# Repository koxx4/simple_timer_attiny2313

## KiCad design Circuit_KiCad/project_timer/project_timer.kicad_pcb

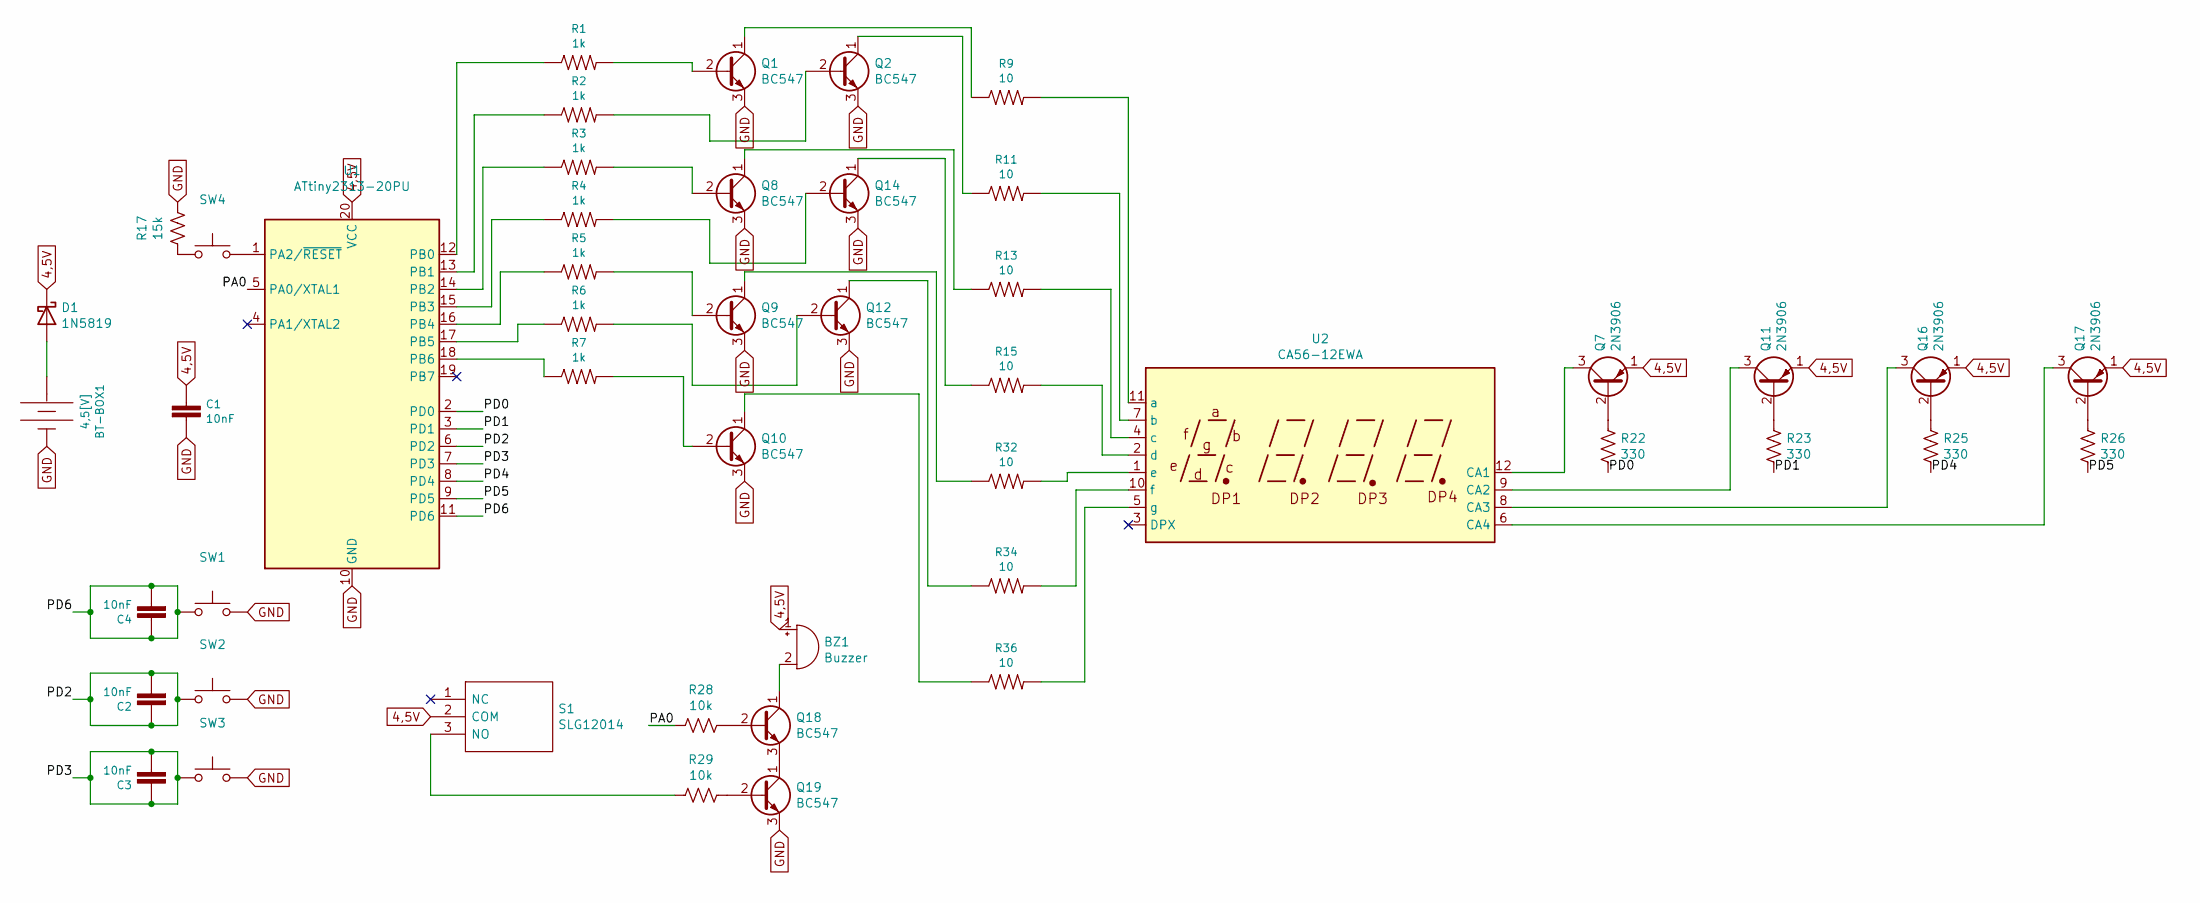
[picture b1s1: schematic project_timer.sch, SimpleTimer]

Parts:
BT-BOX1: 4,5[V]; BatteryHolder_Keystone_2479_3xAAA
BZ1: Buzzer; Buzzer_12x9.5RM7.6
C1, C2, C3, C4: 10nF; C_Disc_D5.0mm_W2.5mm_P2.50mm_1mm-hole
D1: 1N5819; D_DO-15_P10.16mm_Horizontal
Q1, Q2, Q8, Q9, Q10, Q12, Q14, Q18, Q19: BC547; TO-92_HandSolder_1mm
Q7, Q11, Q16, Q17: 2N3906; TO-92_HandSolder_1mm
R1, R2, R3, R4, R5, R6, R7: 1k; R_Axial_DIN0207_L6.3mm_D2.5mm_P2.54mm_Vertical_1mm-hole
R9, R11, R13, R15, R32, R34, R36: 10; R_Axial_DIN0207_L6.3mm_D2.5mm_P2.54mm_Vertical_1mm-hole
R17: 15k; R_Axial_DIN0207_L6.3mm_D2.5mm_P2.54mm_Vertical_1mm-hole
R22, R23, R25, R26: 330; R_Axial_DIN0207_L6.3mm_D2.5mm_P2.54mm_Vertical_1mm-hole
R28, R29: 10k; R_Axial_DIN0207_L6.3mm_D2.5mm_P2.54mm_Vertical_1mm-hole
S1: SLG12014; SLG12014_Bigger; Manufacturer_Part_Number SLG12014; Mouser Part Number 642-SLG12014
SW1, SW2, SW3, SW4: SW_MEC_5G; SW_PUSH_6mm
U1: ATtiny2313-20PU; DIP-20_W7.62mm_Socket_1mm-hole
U2: CA56-12EWA

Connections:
4,5V: BZ1.1 (-), C1.1, D1.1 (K), Q7.1 (E), Q11.1 (E), Q16.1 (E), Q17.1 (E), S1.2 (COM), U1.20 (VCC)
/PA0: R28.2, U1.5 (PA0/XTAL1)
/PD0: R22.2, U1.2 (PD0)
/PD1: R23.2, U1.3 (PD1)
/PD2: C2.1, C2.2, SW2.1 (A), SW2.2 (A), U1.6 (PD2)
/PD3: C3.1, C3.2, SW3.1 (A), SW3.2 (A), U1.7 (PD3)
/PD4: R25.2, U1.8 (PD4)
/PD5: R26.2, U1.9 (PD5)
/PD6: C4.1, C4.2, SW1.1 (A), SW1.2 (A), U1.11 (PD6)
GND: BT-BOX1.2 (-), C1.2, Q1.3 (E), Q2.3 (E), Q8.3 (E), Q9.3 (E), Q10.3 (E), Q12.3 (E), Q14.3 (E), Q19.3 (E), R17.2, SW1.3 (B), SW1.4 (B), SW2.3 (B), SW2.4 (B), SW3.3 (B), SW3.4 (B), U1.10 (GND)
unnamed: BT-BOX1.1 (+), D1.2 (A)
unnamed: BZ1.2 (+), Q18.1 (C)
unnamed: Q1.1 (C), R9.1
unnamed: Q1.2 (B), R1.2
unnamed: Q2.1 (C), R11.1
unnamed: Q2.2 (B), R2.2
unnamed: Q7.2 (B), R22.1
unnamed: Q7.3 (C), U2.12 (CA1)
unnamed: Q8.1 (C), R13.1
unnamed: Q8.2 (B), R3.2
unnamed: Q9.1 (C), R32.1
unnamed: Q9.2 (B), R5.2
unnamed: Q10.1 (C), R36.1
unnamed: Q10.2 (B), R7.2
unnamed: Q11.2 (B), R23.1
unnamed: Q11.3 (C), U2.9 (CA2)
unnamed: Q12.1 (C), R34.1
unnamed: Q12.2 (B), R6.2
unnamed: Q14.1 (C), R15.1
unnamed: Q14.2 (B), R4.2
unnamed: Q16.2 (B), R25.1
unnamed: Q16.3 (C), U2.8 (CA3)
unnamed: Q17.2 (B), R26.1
unnamed: Q17.3 (C), U2.6 (CA4)
unnamed: Q18.2 (B), R28.1
unnamed: Q18.3 (E), Q19.1 (C)
unnamed: Q19.2 (B), R29.1
unnamed: R1.1, U1.12 (PB0)
unnamed: R2.1, U1.13 (PB1)
unnamed: R3.1, U1.14 (PB2)
unnamed: R4.1, U1.15 (PB3)
unnamed: R5.1, U1.16 (PB4)
unnamed: R6.1, U1.17 (PB5)
unnamed: R7.1, U1.18 (PB6)
unnamed: R9.2, U2.11 (a)
unnamed: R11.2, U2.7 (b)
unnamed: R13.2, U2.4 (c)
unnamed: R15.2, U2.2 (d)
unnamed: R17.1, SW4.1 (A), SW4.2 (A)
unnamed: R29.2, S1.3 (NO)
unnamed: R32.2, U2.1 (e)
unnamed: R34.2, U2.10 (f)
unnamed: R36.2, U2.5 (g)
unnamed: SW4.3 (B), SW4.4 (B), U1.1 (PA2/~RESET)

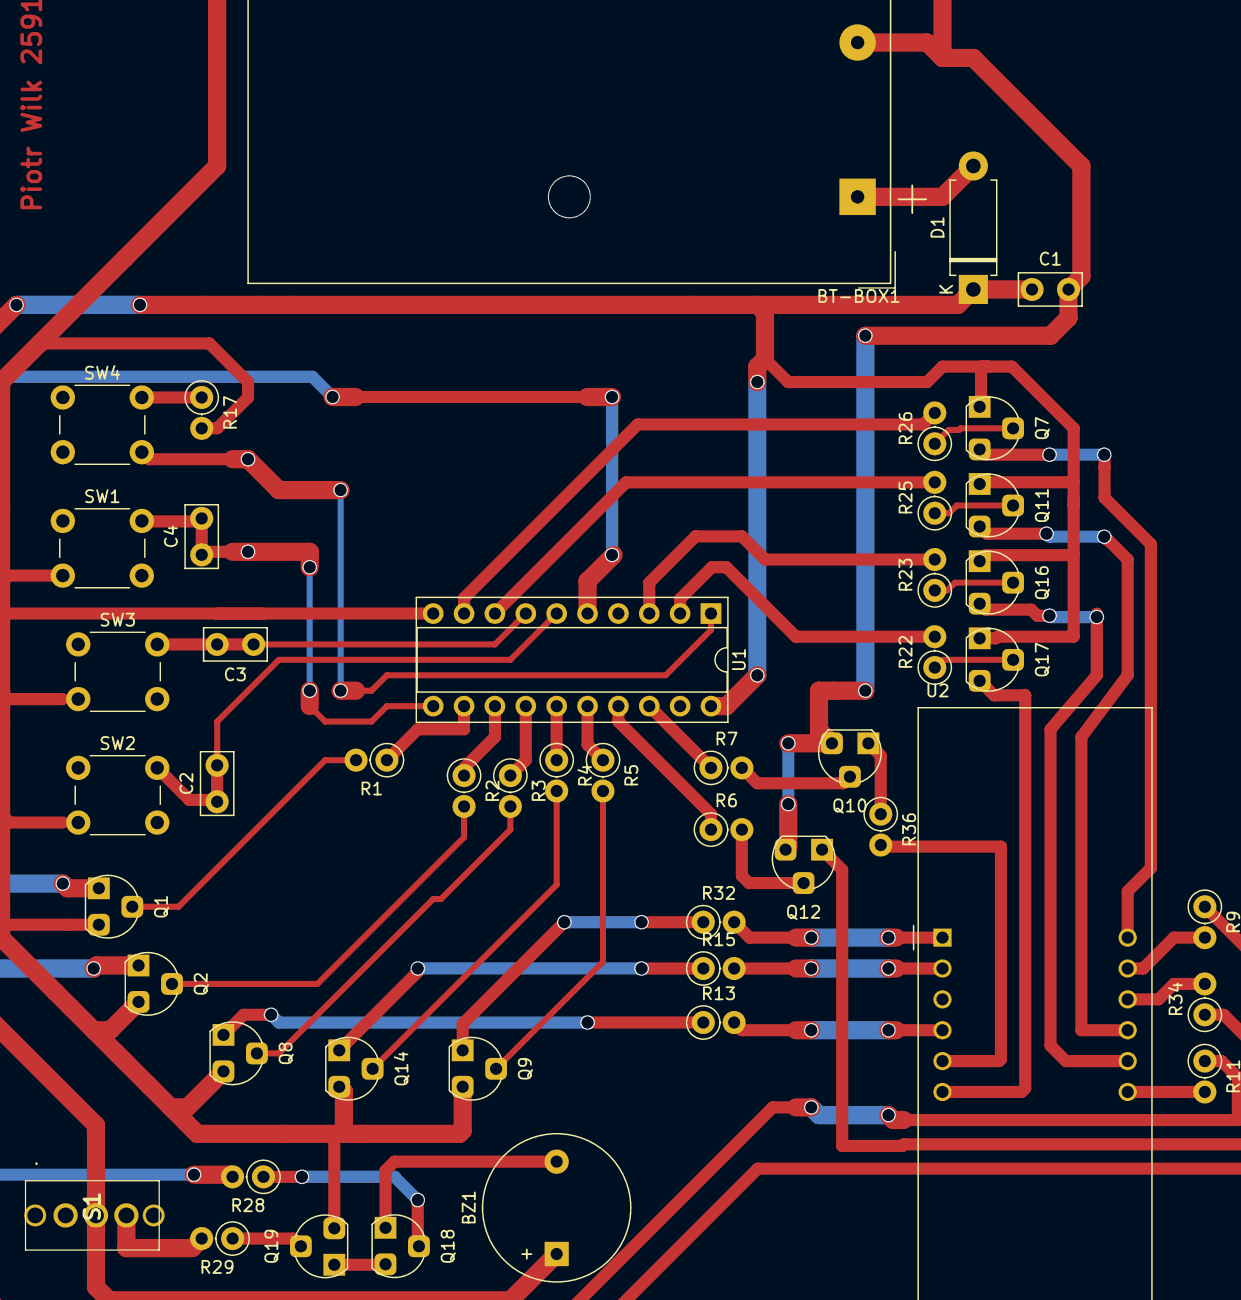
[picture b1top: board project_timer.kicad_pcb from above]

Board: 2 copper layers, 48 parts (0 on the bottom side), 54 nets.

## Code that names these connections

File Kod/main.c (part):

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#define HOUR_L_PART 1
#define HOUR_H_PART 0

#define S_A (1<<PB0)
#define S_B (1<<PB1)
#define S_C (1<<PB2)
#define S_D (1<<PB3)
#define S_E (1<<PB4)
#define S_F (1<<PB5)
#define S_G (1<<PB6)
#define S_DP (1<<PB7)

#define DISP_1 PD5
#define DISP_2 PD4
#define DISP_3 PD1
#define DISP_4 PD0

#define DC_PWM_BUTTON PD6
#define BUTTON_1 PD2
#define BUTTON_2 PD3
#define BUZZ_PIN PA0

#define TurnOnDisplay(display) (PORTD &= ~(1 << display))
#define TurnOffDisplay(display) (PORTD |= (1 << display))
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#define NUM_TWO (S_A|S_B|S_G|S_E|S_D)
#define NUM_THREE (S_A|S_B|S_G|S_C|S_D)
#define NUM_FOUR (S_B|S_F|S_G|S_C)
#define NUM_FIVE ((1 << PB0)|(1 << PB5)|(1 << PB6)|(1 << PB2)|(1 << PB3))
#define NUM_SIX ((1 << PB0)|(1 << PB5)|(1 << PB6)|(1 << PB4)|(1 << PB2)|(1 << PB3))
#define NUM_SEVEN (S_A|S_B|S_C)
#define NUM_EIGHT (NUM_ZERO|S_G)
#define NUM_NINE (NUM_SEVEN|S_F|S_G)
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})

#define Initialize() ({\
	DDRB = (1 << PB7) | (1 << PB6) | (1 << PB5) | (1 << PB4) | (1 << PB3) | (1 << PB2)| (1 << PB1)| (1 << PB0);\
	DDRD = (1 << PD0) | (1 << PD1) | (1 << PD4) | (1 << PD5);\
	DDRA = (1 << BUZZ_PIN);\
	PORTD = (1 << DC_PWM_BUTTON)|(1 << BUTTON_1)|(1 << BUTTON_2);\
	/* External interrupt for btn1 and btn2 are set when they're low*/\
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
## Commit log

2021-06-21 added some photos
2021-06-25 Create LICENSE
2021-06-25 Create AVR-LIBC COPYRIGHT
